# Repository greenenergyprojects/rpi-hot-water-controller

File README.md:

# rpi-hot-water-controller

This project implements a controller for a hot water boiler (for example the [Austria Email EKR-150U](http://www.austria-email.at/produkte/haengespeicher/register-haengespeicher-ekr/))

The controller is based on a Raspberry PI for high level features like WLAN access an security issues. 
For real time controlling functions the Atmega ATmega324P is used, which has a communication link to the Raspberry via it's UART0 interface.
The microcontroller also implements a Modbus interface via it's UART1 interface.

**Features:**

* Built in 230V/5W supply
* Raspberry PI supporting Ethernet or WLAN access and high level programming
* 1 Microcontroller (Atmgea324P) supporting Modbus RTU (or Modbus-ASCII) and real time programming
* Measurment for temperature sensor inside boiler (PT1000)
* 4-20mA interface for thyristor phase control circuit (for example [Schäcke P0000113](https://www.schaecke.at/aus/Kategorien/Steuern-%26-Regeln/Sch%C3%BCtze-%26-Relais/Halbleiterrelais/Wallner-Automation-Leistungssteller-Thyristor-LS1-3%2C6-230V-40-A-4-20-mA-inkl-KK/p/4122046)) used for smart electric heater control
* Additional sensor interfaces (2x flow sensors 5V/digital pulse, 1x PT1000)
* Four solid state relais for 230V/2A
* Interface for four external LEDs or buttons.
* For DIN-rail housing [Camdenboss CBRPP-DR-CLR](https://www.camdenboss.com/camden-boss/cbrpi-dr-2-3-clr-pi-b%2c-p2%2c-p3-din-rail-enclosure/c-23/p-16101)  
(W x H x D = 88mm x 90mm x 58mm; 4.8 DIN rails units)

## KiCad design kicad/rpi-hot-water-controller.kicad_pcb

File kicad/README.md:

https://rn-wissen.de/wiki/index.php/PTC/NTC#Schaltungsbeispiele

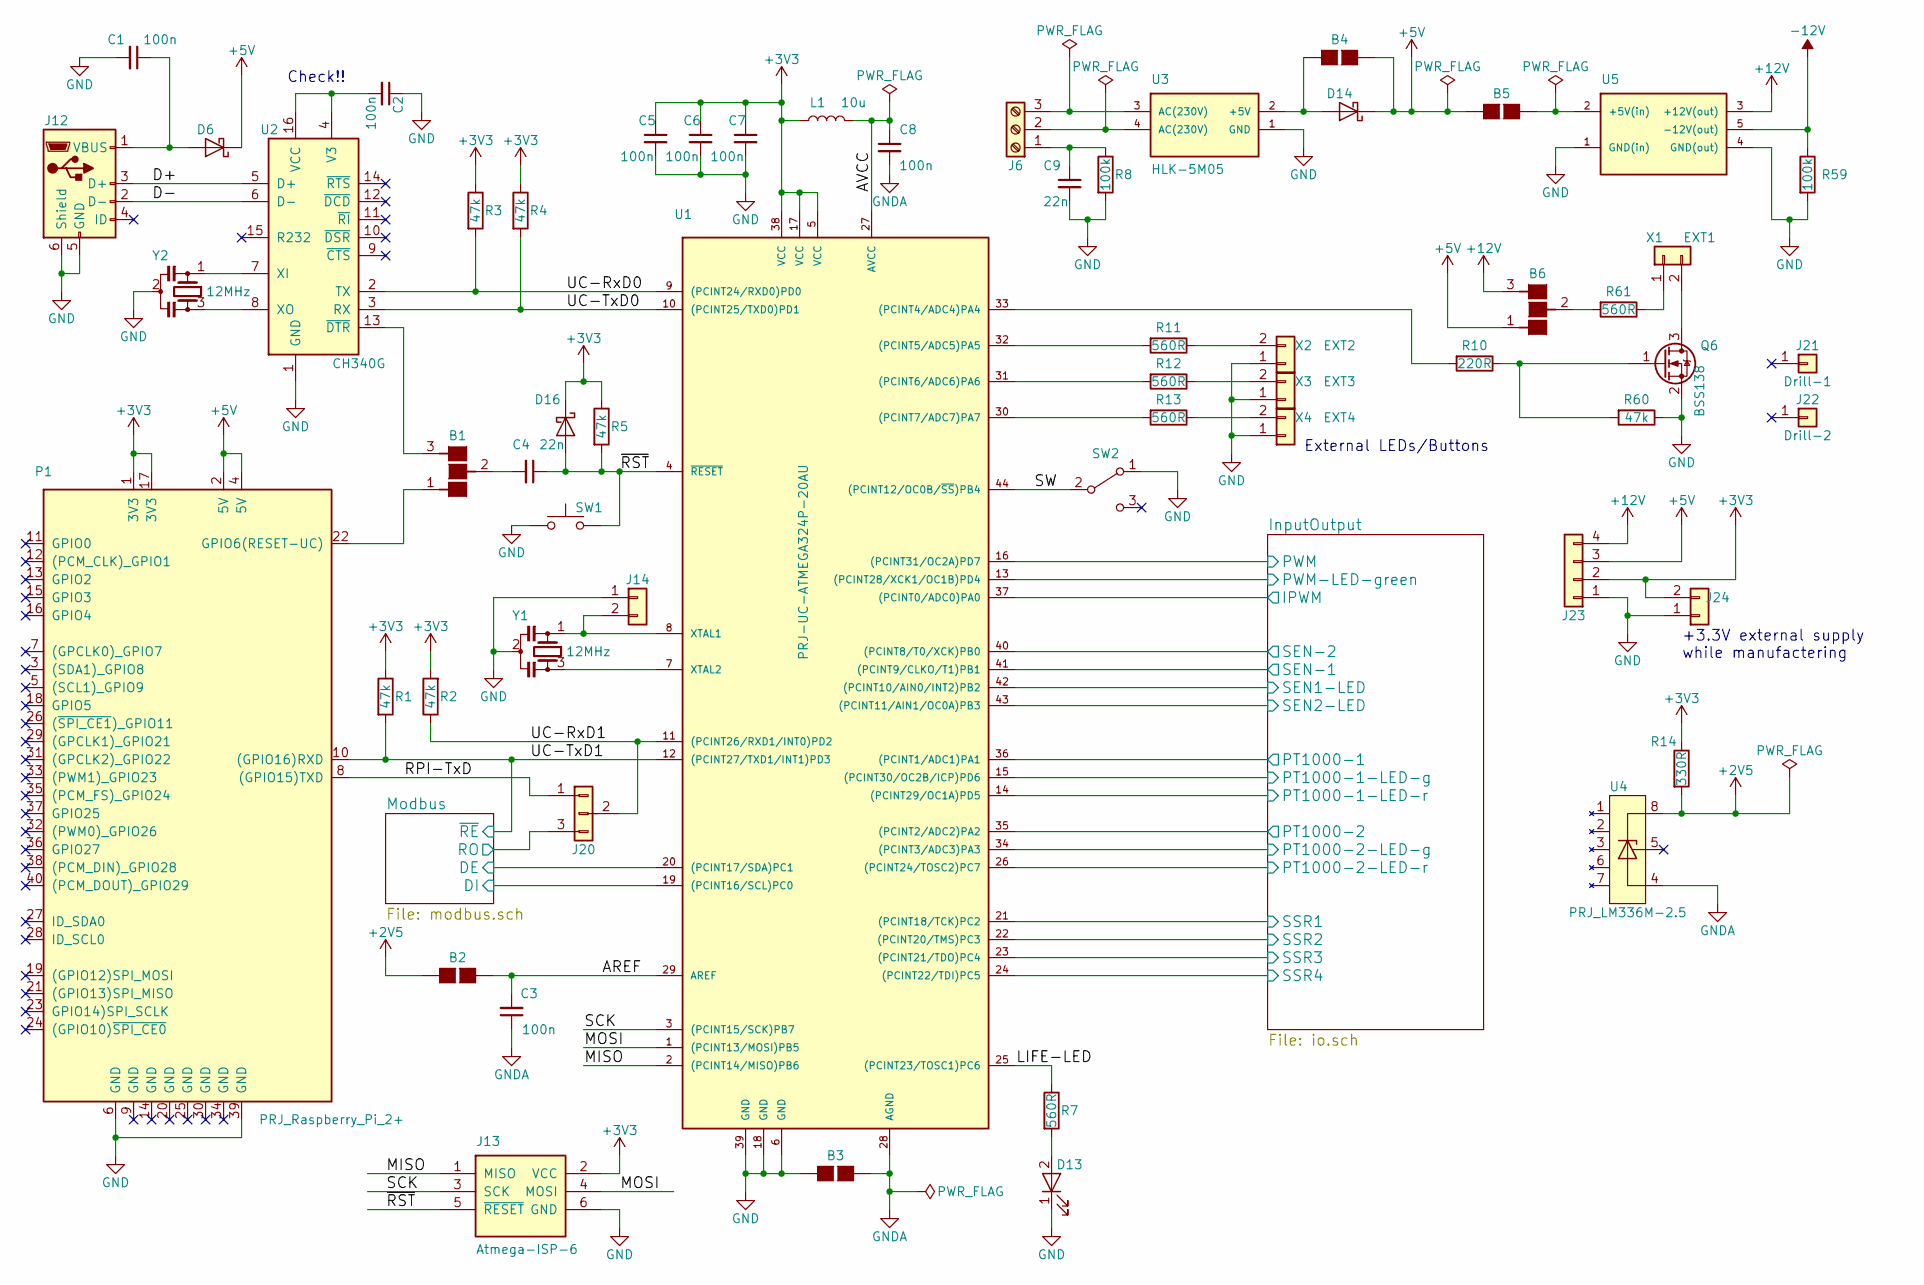
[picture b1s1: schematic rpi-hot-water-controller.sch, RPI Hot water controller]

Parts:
B1, B6: SOLDERBRDIGE-3; SOLDER-JUMPER_2-WAY
B2, B3, B4, B5: SOLDERBRDIGE-2; SOLDER-JUMPER_1-WAY
C1, C2, C3, C5, C6, C7, C8: 100n; C_1206_HandSoldering
C4, C9: 22n; C_1206_HandSoldering
D6, D14: D_Schottky; D_2114
D13: blue; LED_0805_HandSoldering
D16: D_Schottky; D_0805
J6: Screw_Terminal_01x03; Terminalblock-3x-5mm_ebay-262602134567
J12: PRJ_USB_MINI; USB_Mini-B-THT
J13: Atmega-ISP-6; IDC_2x3x2.54mm_Straight
J14: Conn_01x02; Pin_Header_Straight_1x02_Pitch2.54mm
J20: PRJ_Conn_01x03; Pin_Header_Straight_1x03_Pitch2.54mm
J21: Drill-1; MountingHole_2.5mm_Pad
J22: Drill-2; MountingHole_2.5mm_Pad
J23: Conn_01x04; Pin_Header_Straight_1x04_Pitch2.00mm
J24: TEST; Pin_Header_Straight_1x02_Pitch2.54mm
L1: 10u; L_1206_HandSoldering
P1: PRJ_Raspberry_Pi_2+; PRJ_Raspberry-PI
Q6: BSS138; SOT-23_Handsoldering
R1, R2, R3, R4, R5, R60: 47k; R_1206_HandSoldering
R7, R11, R12, R13, R61: 560R; R_1206_HandSoldering
R8, R59: 100k; R_1206_HandSoldering
R10: 220R; R_1206_HandSoldering
R14: 330R; R_1206_HandSoldering
SW1: SW_Push; SW_SPST_FSMSM
SW2: SW On/Off; SW_ebay-171865305033
U1: PRJ-UC-ATMEGA324P-20AU; TQFP-44_10x10mm_Pitch0.8mm_Handsolded
U2: CH340G; SOIC-16_3.9x9.9mm_Pitch1.27mm_HANDSOLDERED
U3: HLK-5M05; HLK_5M05
U4: PRJ_LM336M-2.5; SOIC-8_3.9x4.9mm_Pitch1.27mm_Handsolded
U5: PRJ-supply-5VtoPM12V_ebay-253052736386; ebay-253052736386
X1: EXT1; Pin_Header_Straight_1x02_Pitch2.00mm
X2: EXT2; Pin_Header_Straight_1x02_Pitch2.00mm
X3: EXT3; Pin_Header_Straight_1x02_Pitch2.00mm
X4: EXT4; Pin_Header_Straight_1x02_Pitch2.00mm
Y1, Y2: 12MHz; Resonator-3pin_w7.0mm_h2.5mm

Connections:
+2V5: B2.1 (G1), R14.2, U4.8 (+); also elsewhere on the board
+5V: B4.1 (G1), B5.2 (G2), B6.1 (G1), D6.1 (K), D14.1 (K), J23.3, P1.2 (5V), P1.4 (5V); also elsewhere on the board
+12V: B4.3, B6.3 (G3), J23.4, U5.3 (+12V(out)); also elsewhere on the board
-12V: R59.1, U5.5 (-12V(out))
/AREF: B2.2 (G2), C3.2, U1.29 (AREF)
/AVCC: C8.1, L1.2, U1.27 (AVCC)
/D+: J12.3 (D+), U2.5 (D+)
/D-: J12.2 (D-), U2.6 (D-)
/InputOutput/IPWM: U1.37 ((PCINT0/ADC0)PA0); also elsewhere on the board
/InputOutput/PT1000-1: U1.36 ((PCINT1/ADC1)PA1); also elsewhere on the board
/InputOutput/PT1000-1-LED-g: U1.15 ((PCINT30/OC2B/ICP)PD6); also elsewhere on the board
/InputOutput/PT1000-1-LED-r: U1.14 ((PCINT29/OC1A)PD5); also elsewhere on the board
/InputOutput/PT1000-2: U1.35 ((PCINT2/ADC2)PA2); also elsewhere on the board
/InputOutput/PT1000-2-LED-g: U1.34 ((PCINT3/ADC3)PA3); also elsewhere on the board
/InputOutput/PT1000-2-LED-r: U1.26 ((PCINT24/TOSC2)PC7); also elsewhere on the board
/InputOutput/PWM: U1.16 ((PCINT31/OC2A)PD7); also elsewhere on the board
/InputOutput/PWM-LED-green: U1.13 ((PCINT28/XCK1/OC1B)PD4); also elsewhere on the board
/InputOutput/SEN1-LED: U1.42 ((PCINT10/AIN0/INT2)PB2); also elsewhere on the board
/InputOutput/SEN2-LED: U1.43 ((PCINT11/AIN1/OC0A)PB3); also elsewhere on the board
/InputOutput/SEN-1: U1.41 ((PCINT9/CLKO/T1)PB1); also elsewhere on the board
/InputOutput/SEN-2: U1.40 ((PCINT8/T0/XCK)PB0); also elsewhere on the board
/InputOutput/SSR1: U1.21 ((PCINT18/TCK)PC2); also elsewhere on the board
/InputOutput/SSR2: U1.22 ((PCINT20/TMS)PC3); also elsewhere on the board
/InputOutput/SSR3: U1.23 ((PCINT21/TDO)PC4); also elsewhere on the board
/InputOutput/SSR4: U1.24 ((PCINT22/TDI)PC5); also elsewhere on the board
/LIFE-LED: R7.1, U1.25 ((PCINT23/TOSC1)PC6)
/MISO: J13.1 (MISO), U1.2 ((PCINT14/MISO)PB6)
/MOSI: J13.4 (MOSI), U1.1 ((PCINT13/MOSI)PB5)
/Modbus/DE: U1.20 ((PCINT17/SDA)PC1); also elsewhere on the board
/Modbus/DI: U1.19 ((PCINT16/SCL)PC0); also elsewhere on the board
/Modbus/RO: J20.3; also elsewhere on the board
/RPI-TxD: J20.1, P1.8 ((GPIO15)TXD)
/SCK: J13.3 (SCK), U1.3 ((PCINT15/SCK)PB7)
/SW: SW2.2 (B), U1.44 ((PCINT12/OC0B/~SS~)PB4)
/UC-RxD0: R3.2, U1.9 ((PCINT24/RXD0)PD0), U2.2 (TX)
/UC-RxD1: J20.2, R2.1, U1.11 ((PCINT26/RXD1/INT0)PD2)
/UC-TxD0: R4.2, U1.10 ((PCINT25/TXD0)PD1), U2.3 (RX)
/UC-TxD1: P1.10 ((GPIO16)RXD), R1.2, U1.12 ((PCINT27/TXD1/INT1)PD3); also elsewhere on the board
/~RST~: C4.1, D16.2 (A), J13.5 (~RESET~), R5.2, SW1.2, U1.4 (~RESET)
GND: B3.2 (G2), C1.2, C2.1, C5.2, C6.2, C7.2, C9.2, D13.1 (K), J12.5 (GND), J12.6 (Shield), J13.6 (GND), J14.1, J23.1, J24.1, P1.6 (GND), P1.39 (GND), Q6.2 (S), R8.2, R59.2, R60.1, SW1.1, SW2.1 (A), U1.6 (GND), U1.18 (GND), U1.39 (GND), U2.1 (GND), U3.1 (GND), U5.1 (GND(in)), U5.4 (GND(out)), X2.1, X3.1, X4.1, Y1.2, Y2.2; also elsewhere on the board
GNDA: B3.1 (G1), C3.1, C8.2, U1.28 (AGND), U4.4 (-); also elsewhere on the board
unnamed: B1.1 (G1), P1.22 (GPIO6(RESET-UC))
unnamed: B1.2 (G2), C4.2
unnamed: B1.3 (G3), U2.13 (~DTR~)
unnamed: B5.1 (G1), U5.2 (+5V(in))
unnamed: C9.1, J6.1, R8.1
unnamed: D13.2 (A), R7.2
unnamed: J6.2, U3.4 (AC(230V))
unnamed: J6.3, U3.3 (AC(230V))
unnamed: J14.2, U1.8 (XTAL1), Y1.1
unnamed: Q6.1 (G), R10.1, R60.2
unnamed: Q6.3 (D), X1.2
unnamed: R10.2, U1.33 ((PCINT4/ADC4)PA4)
unnamed: R11.1, X2.2
unnamed: R11.2, U1.32 ((PCINT5/ADC5)PA5)
unnamed: R12.1, X3.2
unnamed: R12.2, U1.31 ((PCINT6/ADC6)PA6)
unnamed: R13.1, X4.2
unnamed: R13.2, U1.30 ((PCINT7/ADC7)PA7)
unnamed: R61.1, X1.1
unnamed: U1.7 (XTAL2), Y1.3
unnamed: U2.7 (XI), Y2.1
unnamed: U2.8 (XO), Y2.3

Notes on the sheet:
Check!!
External LEDs/Buttons
+3.3V external supply while manufactering

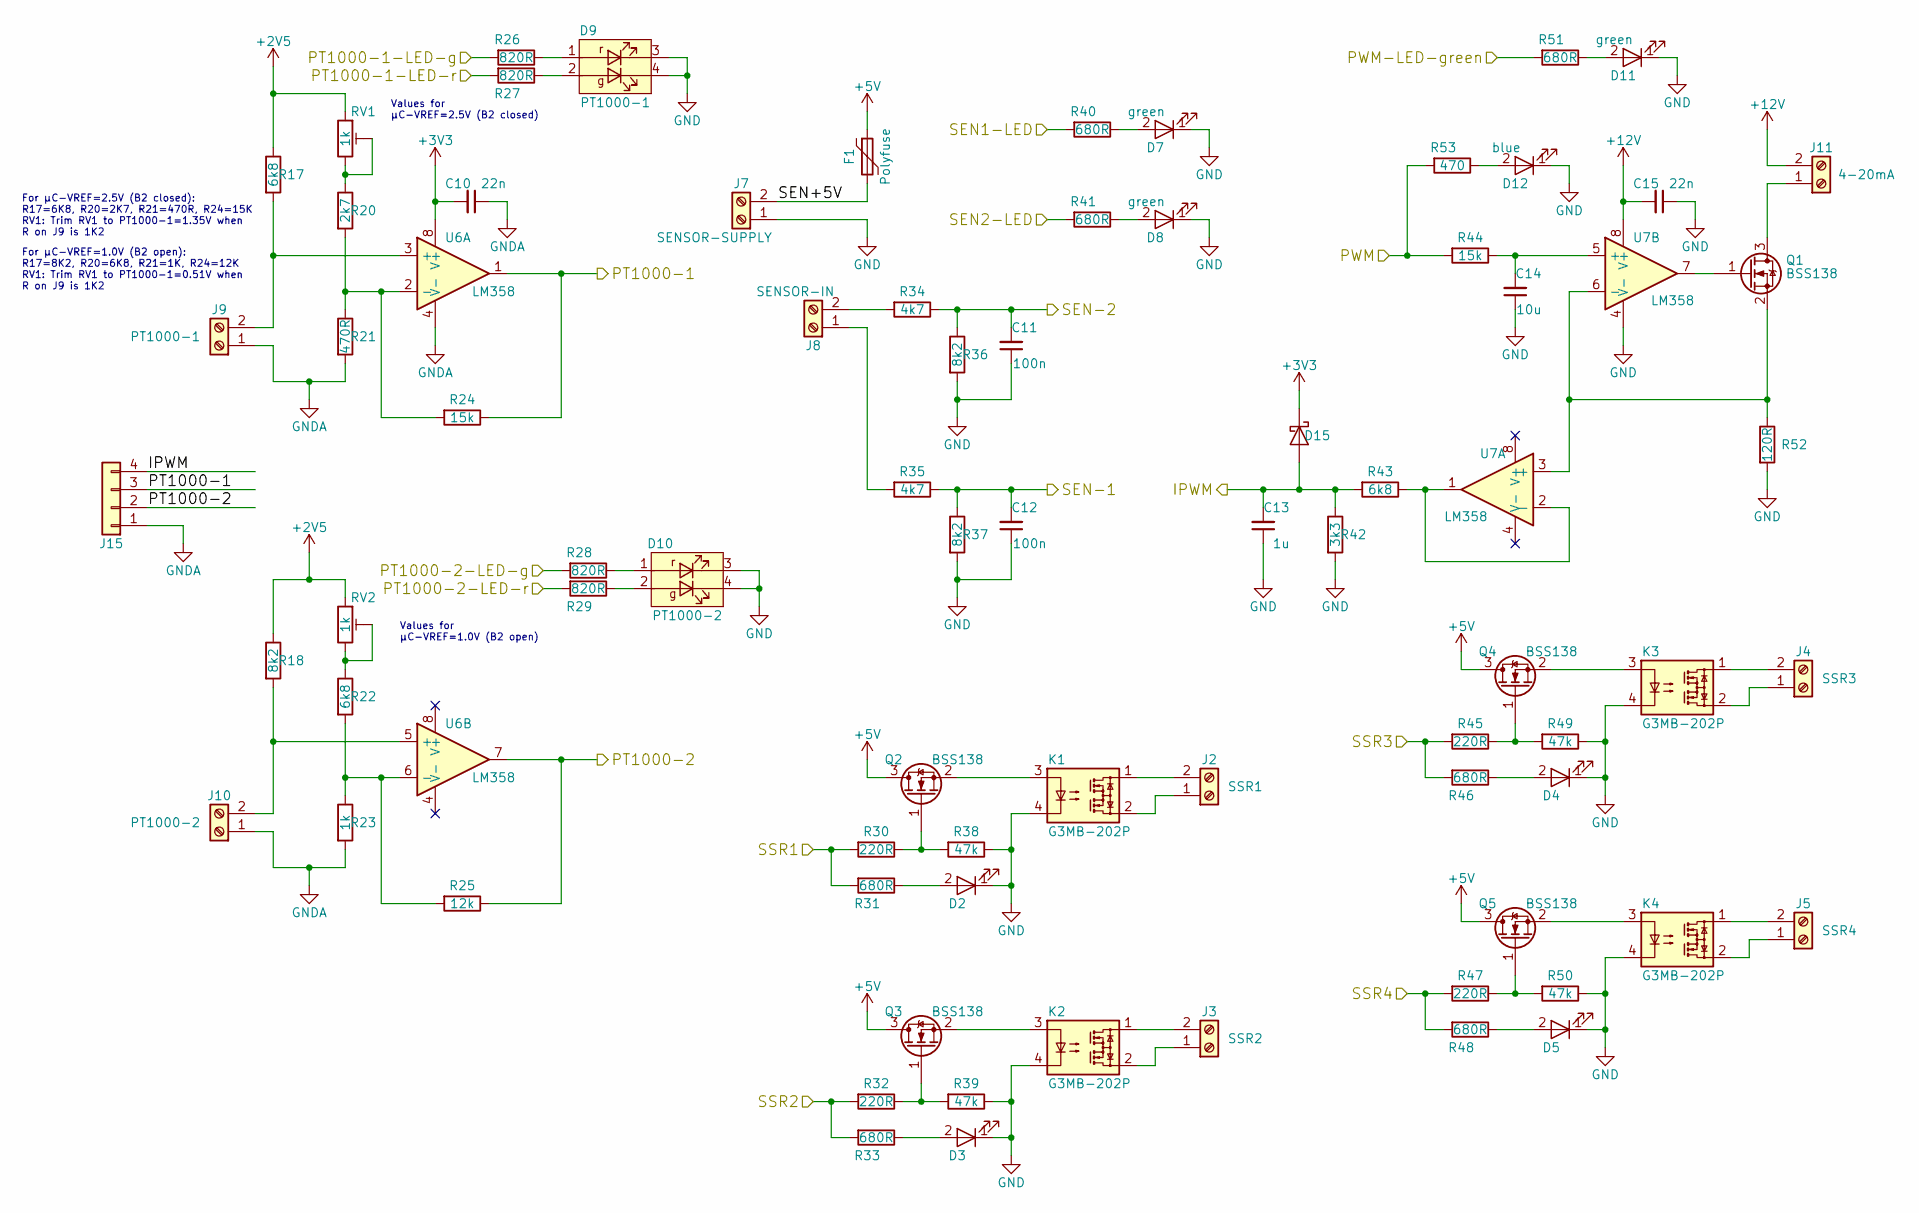
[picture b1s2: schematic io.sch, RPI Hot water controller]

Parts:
C10, C15: 22n; C_1206_HandSoldering
C11, C12: 100n; C_1206_HandSoldering
C13: 1u; C_1206_HandSoldering
C14: 10u; C_1206_HandSoldering
D2, D3, D4, D5, D12: blue; LED_0805_HandSoldering
D7, D8, D11: green; LED_0805_HandSoldering
D9: PT1000-1; LED_Bi-Color-1206_ebay-381282302537
D10: PT1000-2; LED_Bi-Color-1206_ebay-381282302537
D15: D_Schottky; LED_0805_HandSoldering
F1: Polyfuse; R_1812_HandSoldering
J2: SSR1; Terminalblock-2x-5,08mm_ebay-273426629807
J3: SSR2; Terminalblock-2x-5,08mm_ebay-273426629807
J4: SSR3; Terminalblock-2x-5,08mm_ebay-273426629807
J5: SSR4; Terminalblock-2x-5,08mm_ebay-273426629807
J7: SENSOR-SUPPLY; Terminalblock-2x-5,08mm_ebay-273426629807
J8: SENSOR-IN; Terminalblock-2x-5,08mm_ebay-273426629807
J9: PT1000-1; Terminalblock-2x-5,08mm_ebay-273426629807
J10: PT1000-2; Terminalblock-2x-5,08mm_ebay-273426629807
J11: 4-20mA; Terminalblock-2x-5,08mm_ebay-273426629807
J15: Conn_01x04; Pin_Header_Straight_1x04_Pitch2.54mm
K1, K2, K3, K4: G3MB-202P; SSR_Omron_G3MB-202P
Q1, Q2, Q3, Q4, Q5: BSS138; SOT-23_Handsoldering
R17, R22, R43: 6k8; R_1206_HandSoldering
R18, R36, R37: 8k2; R_1206_HandSoldering
R20: 2k7; R_1206_HandSoldering
R21: 470R; R_1206_HandSoldering
R23: 1k; R_1206_HandSoldering
R24, R44: 15k; R_1206_HandSoldering
R25: 12k; R_1206_HandSoldering
R26, R27, R28, R29: 820R; R_1206_HandSoldering
R30, R32, R45, R47: 220R; R_1206_HandSoldering
R31, R33, R40, R41, R46, R48, R51: 680R; R_1206_HandSoldering
R34, R35: 4k7; R_1206_HandSoldering
R38, R39, R49, R50: 47k; R_1206_HandSoldering
R42: 3k3; R_1206_HandSoldering
R52: 120R; R_1206_HandSoldering
R53: 470; R_1206_HandSoldering
RV1, RV2: 1k; Potentiometer_Trimmer_Bourns_3296W
U6, U7: LM358; SOIC-8_3.9x4.9mm_Pitch1.27mm_Handsolded

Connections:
+2V5: R17.1, R18.1, RV1.1, RV2.1; also elsewhere on the board
+5V: F1.1, Q2.3 (D), Q3.3 (D), Q4.3 (D), Q5.3 (D); also elsewhere on the board
+12V: C15.2, J11.2, U7.8 (V+); also elsewhere on the board
/InputOutput/IPWM: C13.2, D15.2 (A), J15.4, R42.1, R43.2; also elsewhere on the board
/InputOutput/PT1000-1: J15.3, R24.1, U6.1; also elsewhere on the board
/InputOutput/PT1000-1-LED-g: R26.2; also elsewhere on the board
/InputOutput/PT1000-1-LED-r: R27.2; also elsewhere on the board
/InputOutput/PT1000-2: J15.2, R25.1, U6.7; also elsewhere on the board
/InputOutput/PT1000-2-LED-g: R28.2; also elsewhere on the board
/InputOutput/PT1000-2-LED-r: R29.2; also elsewhere on the board
/InputOutput/PWM: R44.2, R53.2; also elsewhere on the board
/InputOutput/PWM-LED-green: R51.2; also elsewhere on the board
/InputOutput/SEN1-LED: R40.2; also elsewhere on the board
/InputOutput/SEN2-LED: R41.2; also elsewhere on the board
/InputOutput/SEN+5V: F1.2, J7.2
/InputOutput/SEN-1: C12.2, R35.1, R37.1; also elsewhere on the board
/InputOutput/SEN-2: C11.2, R34.1, R36.1; also elsewhere on the board
/InputOutput/SSR1: R30.2, R31.2; also elsewhere on the board
/InputOutput/SSR2: R32.2, R33.2; also elsewhere on the board
/InputOutput/SSR3: R45.2, R46.2; also elsewhere on the board
/InputOutput/SSR4: R47.2, R48.2; also elsewhere on the board
GND: C11.1, C12.1, C13.1, C14.1, C15.1, D2.1 (K), D3.1 (K), D4.1 (K), D5.1 (K), D7.1 (K), D8.1 (K), D9.3 (K1), D9.4 (K2), D10.3 (K1), D10.4 (K2), D11.1 (K), D12.1 (K), J7.1, K1.4 (-), K2.4 (-), K3.4 (-), K4.4 (-), R36.2, R37.2, R38.1, R39.1, R42.2, R49.1, R50.1, R52.2, U7.4 (V-); also elsewhere on the board
GNDA: C10.1, J9.1, J10.1, J15.1, R21.2, R23.2, U6.4 (V-); also elsewhere on the board
unnamed: C14.2, R44.1, U7.5 (+)
unnamed: D2.2 (A), R31.1
unnamed: D3.2 (A), R33.1
unnamed: D4.2 (A), R46.1
unnamed: D5.2 (A), R48.1
unnamed: D7.2 (A), R40.1
unnamed: D8.2 (A), R41.1
unnamed: D9.1 (A1), R26.1
unnamed: D9.2 (A2), R27.1
unnamed: D10.1 (A1), R28.1
unnamed: D10.2 (A2), R29.1
unnamed: D11.2 (A), R51.1
unnamed: D12.2 (A), R53.1
unnamed: J2.1, K1.2 (AC)
unnamed: J2.2, K1.1 (AC)
unnamed: J3.1, K2.2 (AC)
unnamed: J3.2, K2.1 (AC)
unnamed: J4.1, K3.2 (AC)
unnamed: J4.2, K3.1 (AC)
unnamed: J5.1, K4.2 (AC)
unnamed: J5.2, K4.1 (AC)
unnamed: J8.1, R35.2
unnamed: J8.2, R34.2
unnamed: J9.2, R17.2, U6.3 (+)
unnamed: J10.2, R18.2, U6.5 (+)
unnamed: J11.1, Q1.3 (D)
unnamed: K1.3 (+), Q2.2 (S)
unnamed: K2.3 (+), Q3.2 (S)
unnamed: K3.3 (+), Q4.2 (S)
unnamed: K4.3 (+), Q5.2 (S)
unnamed: Q1.1 (G), U7.7
unnamed: Q1.2 (S), R52.1, U7.3 (+), U7.6 (-)
unnamed: Q2.1 (G), R30.1, R38.2
unnamed: Q3.1 (G), R32.1, R39.2
unnamed: Q4.1 (G), R45.1, R49.2
unnamed: Q5.1 (G), R47.1, R50.2
unnamed: R20.1, RV1.2, RV1.3
unnamed: R20.2, R21.1, R24.2, U6.2 (-)
unnamed: R22.1, RV2.2, RV2.3
unnamed: R22.2, R23.1, R25.2, U6.6 (-)
unnamed: R43.1, U7.1, U7.2 (-)

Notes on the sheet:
For µC-VREF=2.5V (B2 closed): R17=6K8, R20=2K7, R21=470R, R24=15K RV1: Trim RV1 to PT1000-1=1.35V when R on J9 is 1K2
For µC-VREF=1.0V (B2 open): R17=8K2, R20=6K8, R21=1K, R24=12K RV1: Trim RV1 to PT1000-1=0.51V when R on J9 is 1K2
Values for µC-VREF=1.0V (B2 open)
Values for µC-VREF=2.5V (B2 closed)

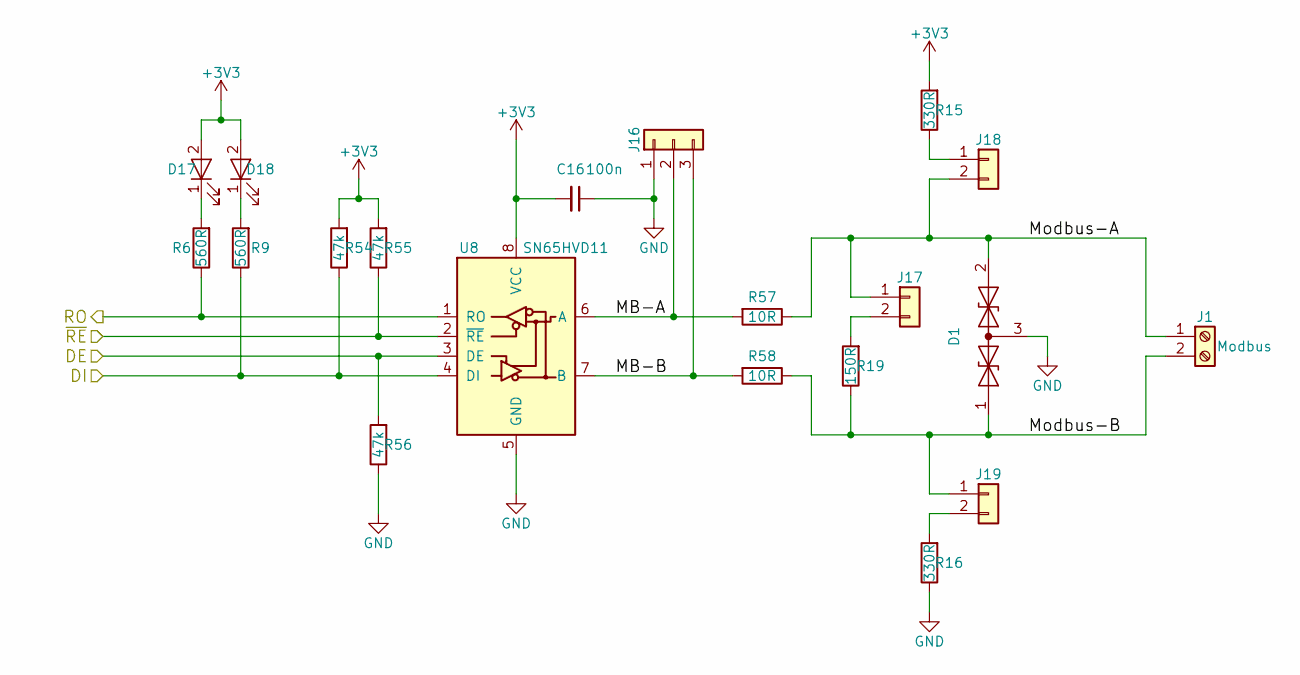
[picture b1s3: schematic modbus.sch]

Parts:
C16: 100n; C_1206_HandSoldering
D1: D_TVS_x2_AAC-RESCUE-rpi-atmega324-modbus-x3-gatew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; SOT-23_Handsoldering
D17: RX; LED_0805_HandSoldering
D18: TX; LED_0805_HandSoldering
J1: Modbus; Terminalblock-2x-5,08mm_ebay-273426629807
J16: Conn_01x03; Pin_Header_Straight_1x03_Pitch2.54mm
J17, J18, J19: Conn_01x02; Pin_Header_Straight_1x02_Pitch2.54mm
R6, R9: 560R; R_1206_HandSoldering
R15, R16: 330R; R_1206_HandSoldering
R19: 150R; R_1206_HandSoldering
R54, R55, R56: 47k; R_1206_HandSoldering
R57, R58: 10R; R_1206_HandSoldering
U8: SN65HVD11; SOIC-8_3.9x4.9mm_Pitch1.27mm_Handsolded

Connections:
/Modbus/DE: R56.2, U8.3 (DE); also elsewhere on the board
/Modbus/DI: R9.1, R54.1, U8.4 (DI); also elsewhere on the board
/Modbus/MB-A: J16.2, R57.2, U8.6 (A)
/Modbus/MB-B: J16.3, R58.2, U8.7 (B)
/Modbus/Modbus-A: D1.2 (A2), J1.1, J17.1, J18.2, R57.1
/Modbus/Modbus-B: D1.1 (A1), J1.2, J19.1, R19.1, R58.1
/Modbus/RO: R6.1, U8.1 (RO); also elsewhere on the board
/UC-TxD1: R55.1, U8.2 (~RE); also elsewhere on the board
GND: C16.1, D1.3 (common), J16.1, R16.1, R56.1, U8.5 (GND); also elsewhere on the board
unnamed: D17.1 (K), R6.2
unnamed: D18.1 (K), R9.2
unnamed: J17.2, R19.2
unnamed: J18.1, R15.1
unnamed: J19.2, R16.2

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
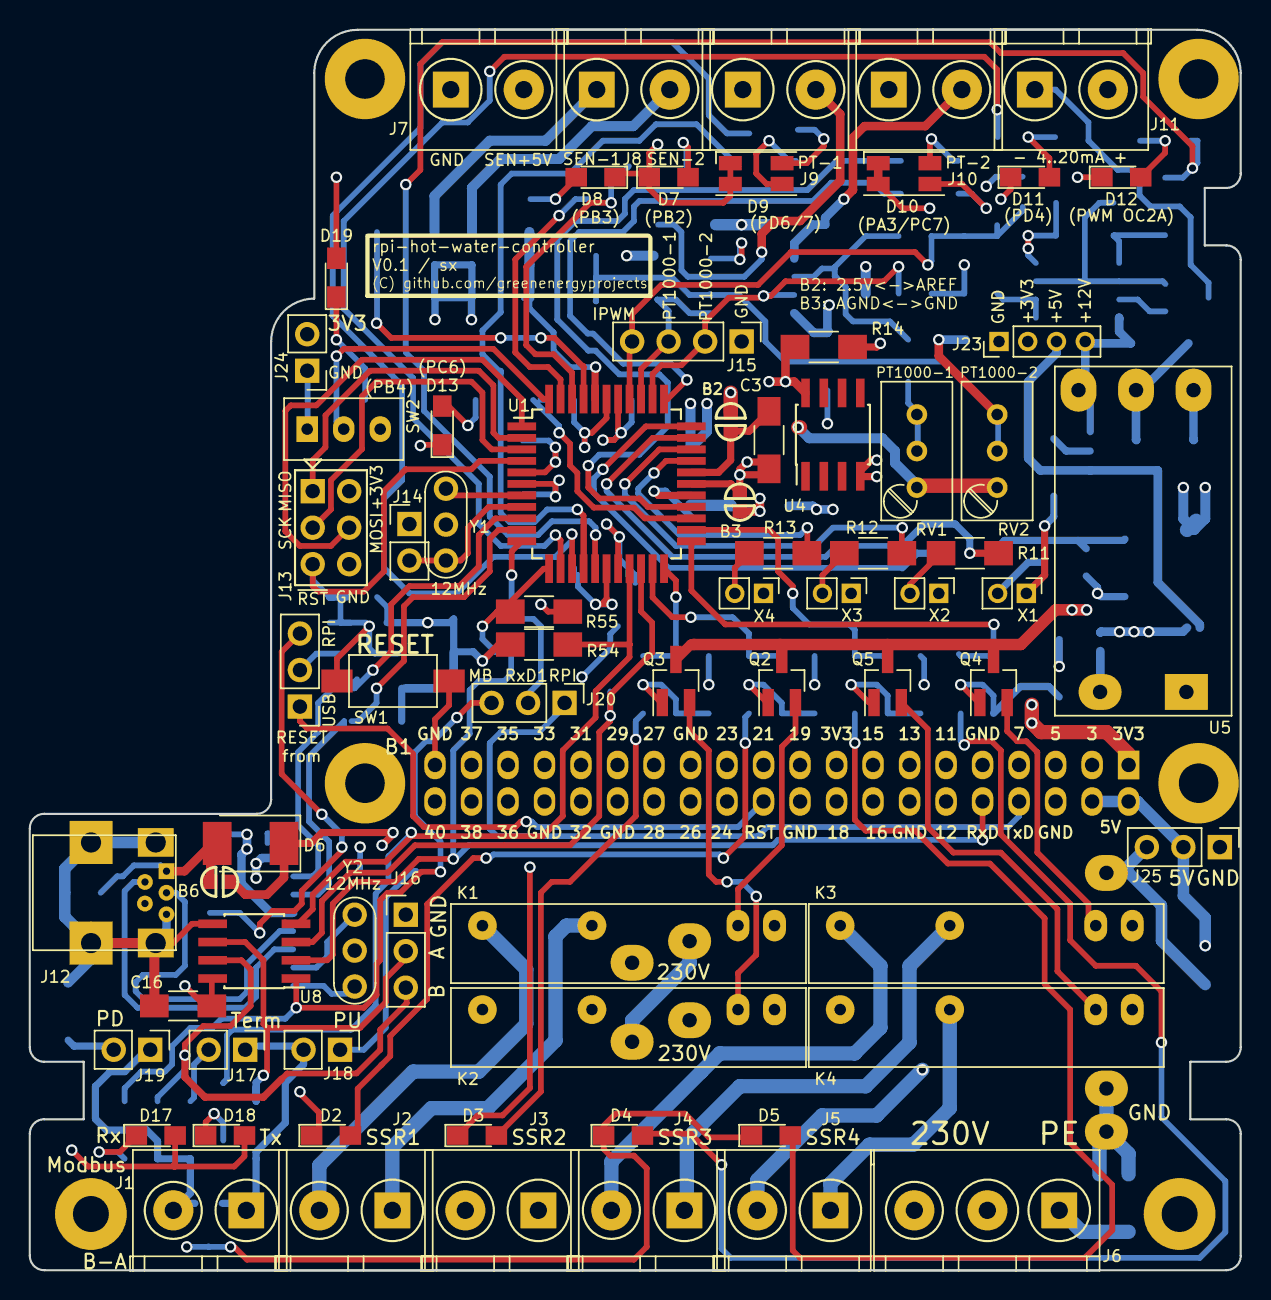
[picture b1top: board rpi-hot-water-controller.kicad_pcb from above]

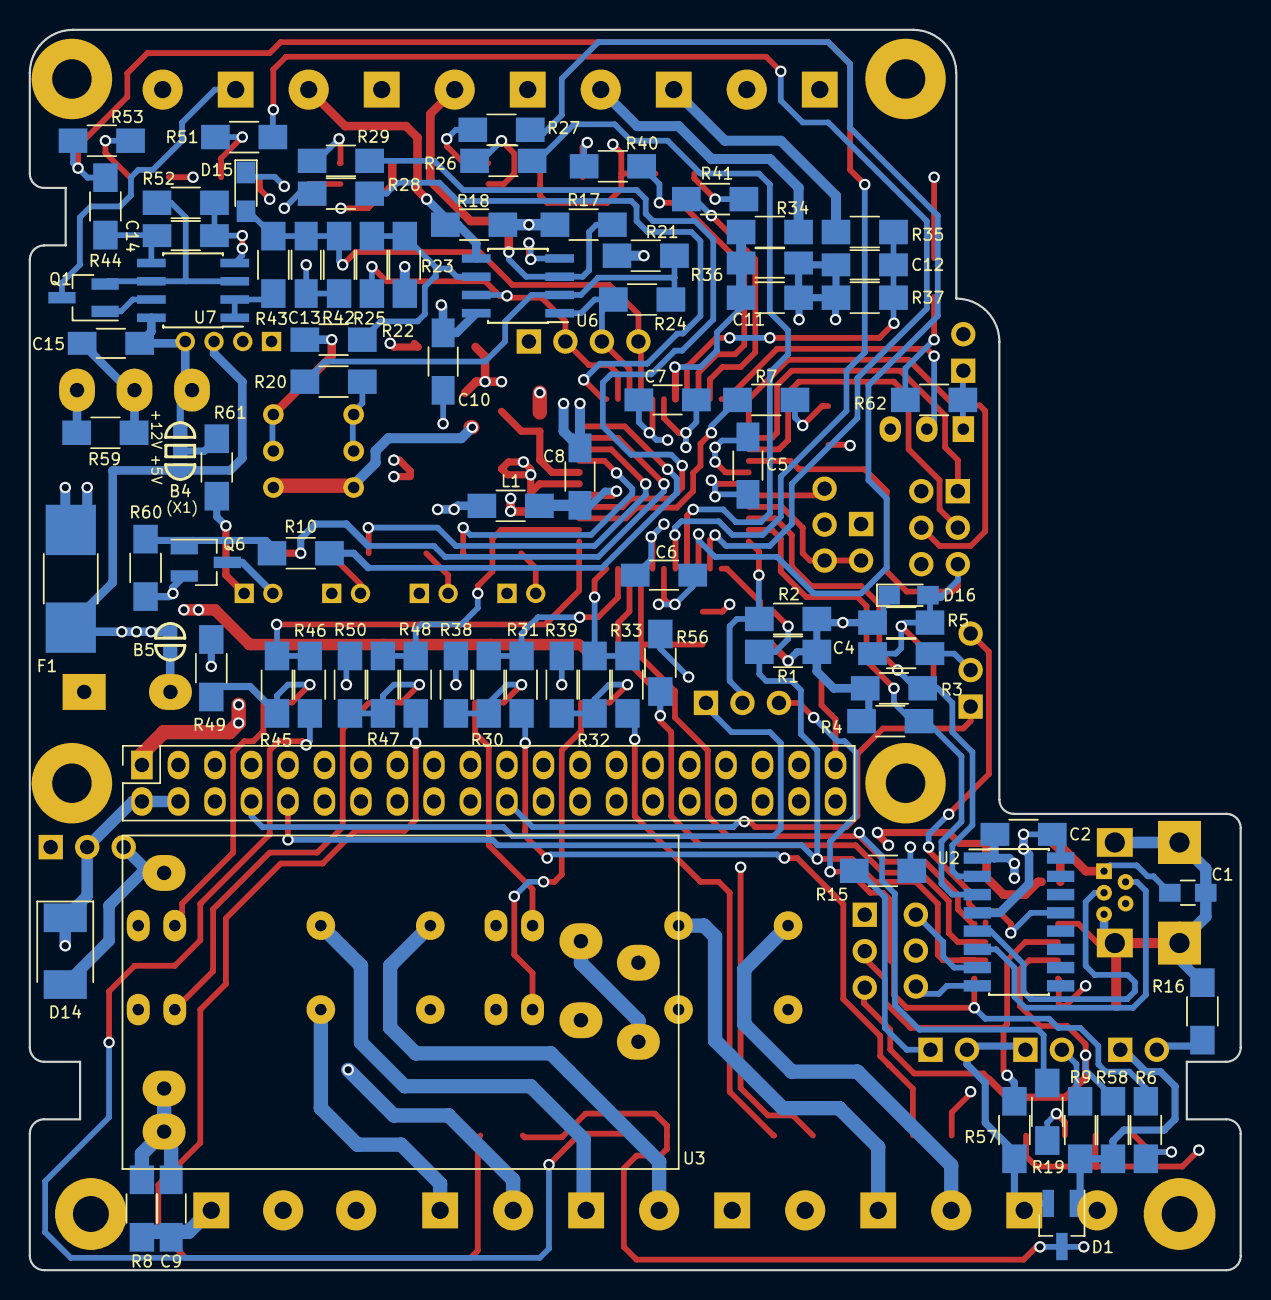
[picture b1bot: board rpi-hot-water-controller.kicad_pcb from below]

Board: 4 copper layers, 84.2 x 86.3 mm, 159 parts (84 on the bottom side), 119 nets.

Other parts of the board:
D19: green; LED_0805_HandSoldering
J25: Conn_01x03; Pin_Header_Straight_1x03_Pitch2.54mm
R62: 680R; R_1206_HandSoldering

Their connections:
+5V: J25.2; also elsewhere on the board
GND: J25.1, R62.1; also elsewhere on the board
unnamed: D19.1, R62.2

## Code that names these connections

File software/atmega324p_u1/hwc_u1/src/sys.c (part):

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
    DDRA |= 0x08;          // LEDs: PT1000-2-g
    DDRB |= 0x0c;          // LEDs: SEN-1, SEN-2
    DDRB &= ~(1 << PB0);   // Sensor 2
    DDRB &= ~(1 << PB1);   // Sensor 1 / S0 Energymeter
    DDRB &= ~(1 << PB4);   // Switch SW2
    PORTB |= (1 << PB4);
    DDRC |= 0xc0;          // LEDs: PT1000-2-r, Life
    DDRC |= 0x3c;          // SSR4, SSR3, SSR2, SSR1
    DDRD |= 0x70;          // LEDs: PT1000-1-g, PT1000-1-r, LED Pwm-Green
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    TCCR2A = (1 << COM2A1) | (1 << COM2A0) | (1 << WGM21) | (1 << WGM20);
    TCCR2B = (1 << CS20);
    OCR2A = 0xff;
    DDRD |= (1 << PD7);    // PWM

    // PORTD |= (1 << PD7);
    // PORTD &= ~(1 << PD6);
    // DDRD |= 0xc0;  // PD7=nModbus1_RE, PD6=Modbus1_DE

    // Timer 0 for task machine
    OCR0A  = (F_CPU + 4) / 8 / 10000 - 1;
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void sys_setSSR (uint8_t index, uint8_t on) {
    if (on) {
        switch (index) {
            case 0: PORTC |= (1 << PC2); return;
            case 1: PORTC |= (1 << PC3); return;
            case 2: PORTC |= (1 << PC4); return;
            case 3: PORTC |= (1 << PC5); return;
        }
    } else {
        switch (index) {
            case 0: PORTC &= ~(1 << PC2); return;
            case 1: PORTC &= ~(1 << PC3); return;
            case 2: PORTC &= ~(1 << PC4); return;
            case 3: PORTC &= ~(1 << PC5); return;
        }
    }
}
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//****************************************************************************

uint8_t sys_isSw2On () {
    return (PINB & (1 << PB4)) != 0;
}

uint8_t sys_isSensor1On () {
    return (PINB & (1 << PB1)) != 0;
}

uint8_t sys_isSensor2On () {
    return (PINB & (1 << PB0)) != 0;
}


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
void sys_setLedLife (uint8_t on) {
    if (on) {
        PORTC |= (1 << PC6);
    } else {
        PORTC &= ~(1 << PC6);
    }
}

void sys_setLedPT1000Red (uint8_t index, uint8_t on) {
    if (on) {
        switch (index) {
            case 0: PORTD |= (1 << PD5); return;
            case 1: PORTC |= (1 << PC7); return;
        }
        
    } else {
        switch (index) {
            case 0: PORTD &= ~(1 << PD5); return;
            case 1: PORTC &= ~(1 << PC7); return;
        }
    }
}
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void sys_setLedPT1000Green (uint8_t index, uint8_t on) {
    if (on) {
        switch (index) {
            case 0: PORTD |= (1 << PD6); return;
            case 1: PORTA |= (1 << PA3); return;
        }
        
    } else {
        switch (index) {
            case 0: PORTD &= ~(1 << PD6); return;
            case 1: PORTA &= ~(1 << PA3); return;
        }
    }
}
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void sys_setLedSensor (uint8_t index, uint8_t on) {
    if (on) {
        switch (index) {
            case 0: PORTB |= (1 << PB3); return;
            case 1: PORTB |= (1 << PB2); return;
        }
        
    } else {
        switch (index) {
            case 0: PORTB &= ~(1 << PB3); return;
            case 1: PORTB &= ~(1 << PB2); return;
        }
    }
}
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
void sys_setLedPwmGreen (uint8_t on) {
    if (on) {
        PORTD |= (1 << PD4);
    } else {
        PORTD &= ~(1 << PD4);
    }
}


void sys_toggleLifeLed () {
    PORTC ^= (1 << PC6);
}

void sys_toggleLedPwmGreen () {
    PORTD ^= (1 << PD4);
}


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
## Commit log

2018-09-20 Project initialization
2018-10-05 first layout finished
2018-10-12 V0.1 Tapeout
2018-10-13 Tapeout V0.1 (gerber update)
2018-11-14 test finished for pcb release V0.1
2018-12-03 4..20mA interface adjustments
2018-12-12 Bootloader for UART0+UART1
2019-01-18 µC S0 interface for energymeter, bugfix hangup
2020-03-05 V0.6.1 (fronius meter defect function)
2020-05-14 boiler contoller bugfix
2020-05-16 boiler smart mode recoded
2020-05-21 smart mode improvements
2020-05-30 boiler smart mode improvements
2020-11-06 V0.8.0 Smart mode bugfix, add parameter minBatLoad
2020-11-06 Bump mixin-deep in /software/rpi/hwc-server-ngx/server
    Bumps [mixin-deep](https://github.com/jonschlinkert/mixin-deep) from 1.3.1 to 1.3.2.
    - [Release notes](https://github.com/jonschlinkert/mixin-deep/releases)
    - [Commits](https://github.com/jonschlinkert/mixin-deep/compare/1.3.1...1.3.2)
2020-11-06 Bump jquery from 3.3.1 to 3.5.1 in /software/rpi/hwc-server-ngx/server
    Bumps [jquery](https://github.com/jquery/jquery) from 3.3.1 to 3.5.1.
    - [Release notes](https://github.com/jquery/jquery/releases)
    - [Commits](https://github.com/jquery/jquery/compare/3.3.1...3.5.1)
2020-11-06 Bump lodash in /software/rpi/hwc-server-ngx/server
    Bumps [lodash](https://github.com/lodash/lodash) from 4.17.11 to 4.17.20.
    - [Release notes](https://github.com/lodash/lodash/releases)
    - [Commits](https://github.com/lodash/lodash/compare/4.17.11...4.17.20)
2020-11-06 Bump bl from 1.2.2 to 1.2.3 in /software/rpi/hwc-server-ngx/server
    Bumps [bl](https://github.com/rvagg/bl) from 1.2.2 to 1.2.3.
    - [Release notes](https://github.com/rvagg/bl/releases)
    - [Commits](https://github.com/rvagg/bl/compare/v1.2.2...v1.2.3)
2020-11-07 V0.8.1 bugfix controller, controller improvements
2020-11-23 V 0.8.2 controller improvements
2020-12-13 Bump ini from 1.3.5 to 1.3.8 in /software/rpi/hwc-server-ngx
    Bumps [ini](https://github.com/isaacs/ini) from 1.3.5 to 1.3.8.
    - [Release notes](https://github.com/isaacs/ini/releases)
    - [Commits](https://github.com/isaacs/ini/compare/v1.3.5...v1.3.8)
2020-12-13 Bump ini from 1.3.5 to 1.3.8 in /software/rpi/flashuc
    Bumps [ini](https://github.com/isaacs/ini) from 1.3.5 to 1.3.8.
    - [Release notes](https://github.com/isaacs/ini/releases)
    - [Commits](https://github.com/isaacs/ini/compare/v1.3.5...v1.3.8)
2020-12-13 Bump ini from 1.3.5 to 1.3.8 in /software/rpi/hwc-server-ngx/server
    Bumps [ini](https://github.com/isaacs/ini) from 1.3.5 to 1.3.8.
    - [Release notes](https://github.com/isaacs/ini/releases)
    - [Commits](https://github.com/isaacs/ini/compare/v1.3.5...v1.3.8)
2021-01-01 controller improvements, V0.8.3
2021-01-05 Test smart batmin 1% -> Pbat = PVsued, V0.8.4
2021-01-14 controller improvement for battery full
2021-03-03 Bump pug-code-gen in /software/rpi/hwc-server-ngx/server
    Bumps [pug-code-gen](https://github.com/pugjs/pug) from 2.0.1 to 2.0.3.
    - [Release notes](https://github.com/pugjs/pug/releases)
    - [Commits](https://github.com/pugjs/pug/compare/pug-code-gen@2.0.1...pug@2.0.3)
2021-03-03 Bump pug from 2.0.3 to 3.0.1 in /software/rpi/hwc-server-ngx/server
    Bumps [pug](https://github.com/pugjs/pug) from 2.0.3 to 3.0.1.
    - [Release notes](https://github.com/pugjs/pug/releases)
    - [Commits](https://github.com/pugjs/pug/compare/pug@2.0.3...pug@3.0.1)
2021-03-11 Bump elliptic from 6.4.1 to 6.5.4 in /software/rpi/hwc-server-ngx/ngx
    Bumps [elliptic](https://github.com/indutny/elliptic) from 6.4.1 to 6.5.4.
    - [Release notes](https://github.com/indutny/elliptic/releases)
    - [Commits](https://github.com/indutny/elliptic/compare/v6.4.1...v6.5.4)
2021-03-31 Bump y18n from 3.2.1 to 3.2.2 in /software/rpi/hwc-server-ngx/server
    Bumps [y18n](https://github.com/yargs/y18n) from 3.2.1 to 3.2.2.
    - [Release notes](https://github.com/yargs/y18n/releases)
    - [Changelog](https://github.com/yargs/y18n/blob/master/CHANGELOG.md)
    - [Commits](https://github.com/yargs/y18n/commits)
2021-03-31 Bump y18n from 3.2.1 to 3.2.2 in /software/rpi/flashuc
    Bumps [y18n](https://github.com/yargs/y18n) from 3.2.1 to 3.2.2.
    - [Release notes](https://github.com/yargs/y18n/releases)
    - [Changelog](https://github.com/yargs/y18n/blob/master/CHANGELOG.md)
    - [Commits](https://github.com/yargs/y18n/commits)
2021-03-31 Bump y18n from 3.2.1 to 3.2.2 in /software/rpi/hwc-server-ngx
    Bumps [y18n](https://github.com/yargs/y18n) from 3.2.1 to 3.2.2.
    - [Release notes](https://github.com/yargs/y18n/releases)
    - [Changelog](https://github.com/yargs/y18n/blob/master/CHANGELOG.md)
    - [Commits](https://github.com/yargs/y18n/commits)
2021-04-01 Bump y18n from 3.2.1 to 3.2.2 in /software/rpi/hwc-server-ngx/ngx
    Bumps [y18n](https://github.com/yargs/y18n) from 3.2.1 to 3.2.2.
    - [Release notes](https://github.com/yargs/y18n/releases)
    - [Changelog](https://github.com/yargs/y18n/blob/master/CHANGELOG.md)
    - [Commits](https://github.com/yargs/y18n/commits)
2021-05-09 Bump handlebars from 4.0.12 to 4.7.7 in /software/rpi/hwc-server-ngx/ngx
    Bumps [handlebars](https://github.com/wycats/handlebars.js) from 4.0.12 to 4.7.7.
    - [Release notes](https://github.com/wycats/handlebars.js/releases)
    - [Changelog](https://github.com/handlebars-lang/handlebars.js/blob/master/release-notes.md)
    - [Commits](https://github.com/wycats/handlebars.js/compare/v4.0.12...v4.7.7)
2021-05-10 Bump url-parse from 1.4.4 to 1.5.1 in /software/rpi/hwc-server-ngx/ngx
    Bumps [url-parse](https://github.com/unshiftio/url-parse) from 1.4.4 to 1.5.1.
    - [Release notes](https://github.com/unshiftio/url-parse/releases)
    - [Commits](https://github.com/unshiftio/url-parse/compare/1.4.4...1.5.1)
2021-05-11 Bump hosted-git-info in /software/rpi/hwc-server-ngx/server
    Bumps [hosted-git-info](https://github.com/npm/hosted-git-info) from 2.7.1 to 2.8.9.
    - [Release notes](https://github.com/npm/hosted-git-info/releases)
    - [Changelog](https://github.com/npm/hosted-git-info/blob/v2.8.9/CHANGELOG.md)
    - [Commits](https://github.com/npm/hosted-git-info/compare/v2.7.1...v2.8.9)
2021-05-11 Bump hosted-git-info in /software/rpi/hwc-server-ngx/ngx
    Bumps [hosted-git-info](https://github.com/npm/hosted-git-info) from 2.7.1 to 2.8.9.
    - [Release notes](https://github.com/npm/hosted-git-info/releases)
    - [Changelog](https://github.com/npm/hosted-git-info/blob/v2.8.9/CHANGELOG.md)
    - [Commits](https://github.com/npm/hosted-git-info/compare/v2.7.1...v2.8.9)
2021-05-11 Bump lodash from 4.17.11 to 4.17.21 in /software/rpi/hwc-server-ngx/ngx
    Bumps [lodash](https://github.com/lodash/lodash) from 4.17.11 to 4.17.21.
    - [Release notes](https://github.com/lodash/lodash/releases)
    - [Commits](https://github.com/lodash/lodash/compare/4.17.11...4.17.21)
2021-05-11 Bump lodash in /software/rpi/hwc-server-ngx/server
    Bumps [lodash](https://github.com/lodash/lodash) from 4.17.11 to 4.17.21.
    - [Release notes](https://github.com/lodash/lodash/releases)
    - [Commits](https://github.com/lodash/lodash/compare/4.17.11...4.17.21)
2021-05-26 Bump browserslist in /software/rpi/hwc-server-ngx/ngx
    Bumps [browserslist](https://github.com/browserslist/browserslist) from 4.3.5 to 4.16.6.
    - [Release notes](https://github.com/browserslist/browserslist/releases)
    - [Changelog](https://github.com/browserslist/browserslist/blob/main/CHANGELOG.md)
    - [Commits](https://github.com/browserslist/browserslist/compare/4.3.5...4.16.6)
2021-05-29 Bump dns-packet from 1.3.1 to 1.3.4 in /software/rpi/hwc-server-ngx/ngx
    Bumps [dns-packet](https://github.com/mafintosh/dns-packet) from 1.3.1 to 1.3.4.
    - [Release notes](https://github.com/mafintosh/dns-packet/releases)
    - [Changelog](https://github.com/mafintosh/dns-packet/blob/master/CHANGELOG.md)
    - [Commits](https://github.com/mafintosh/dns-packet/compare/v1.3.1...v1.3.4)
2021-06-21 Bump set-getter from 0.1.0 to 0.1.1 in /software/rpi/flashuc
    Bumps [set-getter](https://github.com/doowb/set-getter) from 0.1.0 to 0.1.1.
    - [Release notes](https://github.com/doowb/set-getter/releases)
    - [Commits](https://github.com/doowb/set-getter/commits/0.1.1)
    ---
    updated-dependencies:
    - dependency-name: set-getter
